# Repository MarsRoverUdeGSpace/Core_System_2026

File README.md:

# Core System 2026

Core electronics, embedded firmware, and ROS 2 integration workspace for the UdeG Space 2026 rover platform.

## Overview

This repository contains the validated `Kukulcan Rev A` controller hardware, the primary rover MCU firmware, and the ROS 2 workspace used to integrate the embedded system with the rest of the stack.

The current main firmware path, `kukulcan/firmware/upio-ros2/`, is a working ESP32-S3 implementation built on Arduino, FreeRTOS, and micro-ROS, with an AUTOSAR-inspired layered architecture deployed on real hardware.

This MCU sits at the intersection of the rover core system and the autonomous navigation stack for the Mars Rover UdeG Space Maya rover in URC 2026. It concentrates the odometry and control interfaces needed for vehicle state estimation and low-level motion integration, including wheel encoders, dual-IMU integration across the wider system, GNSS, altimeter data, communications with RoboClaw motor controllers, and communications with the main processing unit based on the NVIDIA Jetson Orin Nano.

The platform has already been validated on real hardware and is intended to continue system-level validation during field testing, including work planned for the Mars Desert Research Station.

## Current release state

This repository is past initial bring-up and already contains active work in four areas:

- `kukulcan/hardware/`: KiCad MCU design, 3D exports, fabrication outputs, and PCBA files for `MCU RevA`
- `kukulcan/firmware/upy/`: MicroPython-based sensor and UI bring-up
- `kukulcan/firmware/upio-ros2/`: ESP32-S3 PlatformIO firmware using Arduino, FreeRTOS, micro-ROS, and an AUTOSAR-inspired layered architecture
- `src/`: ROS 2 workspace with custom messages, a local `teleop_twistmux_node`, and vendored micro-ROS packages

As of June 2, 2026, this repository is the stable core-system release line for the rover MCU and ROS-facing embedded interface used by AutoNav.

Current status summary:

- hardware: validated RevA integration board with tracked manufacturing outputs
- firmware: stable release on real hardware with successful `pio run`
- localization interface: firmware-owned epoch-stamped `/odom`, direct BNO055 IMU, magnetometer, and GNSS streams validated on the Kukulcan PCB and consumed by the AutoNav stack
- ROS 2 workspace: active and buildable for the currently used packages
- control interface: `cmd_vel` response and motor timeout behavior corrected for the stable AutoNav integration path

Verified in this repository review:

- `colcon build --packages-select teleop_twistmux_node micro_ros_msgs drive_base_msgs`
- maintainer-provided successful `pio run` result for `upio-ros2`

## Stable release notes

This release promotes `feature/imu-mag-calibration` as the stable source line for `develop` and `main`.

Release highlights:

- integrated wheel odometry publication from RoboClaw encoder ticks
- added BNO055 magnetometer publishing for Jetson-side calibration and localization checks
- stabilized GNSS `NavSatFix`, IMU, magnetometer, and `/odom` timestamps in ROS epoch time
- made `/odom` reliable so full `nav_msgs/msg/Odometry` samples survive XRCE transport size limits
- bounded reliable publisher waits and scheduler catch-up behavior so delayed odometry acknowledgements do not starve IMU/GNSS publication
- calibrated odometry geometry and ticks-per-revolution values for the physical rover
- corrected `cmd_vel` response behavior and retained independent motor safety timeout handling

## Highlights

- `Kukulcan Rev A` is a 4-layer protected controller board built around an `ESP32-S3R8` with added `32 MB` flash
- the firmware architecture treats micro-ROS as the effective RTE boundary and FreeRTOS tasks as the application execution model
- the project has a reliable micro-ROS + FreeRTOS + Arduino implementation on the target MCU
- firmware `/odom` and direct IMU/GNSS topics now provide the validated inputs for Jetson-side EKF/global-localization testing
- the Jetson-side integration path is already designed into the hardware through the 40-pin expansion/control header

## Repository layout

| Path | Purpose |
| --- | --- |
| `kukulcan/hardware/` | MCU KiCad project, local libraries, manufacturing outputs |
| `kukulcan/firmware/` | Embedded firmware projects |
| `src/` | ROS 2 workspace packages and vendored dependencies |
| `docs/` | Datasheets, design notes, images, and release support material |
| `CONTRIBUTING.md` | Lightweight workflow and contribution rules |

## Primary subsystems

- Hardware: [kukulcan/hardware/README.md](kukulcan/hardware/README.md)
- Firmware: [kukulcan/firmware/README.md](kukulcan/firmware/README.md)
- Main firmware track: [kukulcan/firmware/upio-ros2/README.md](kukulcan/firmware/upio-ros2/README.md)

## Firmware architecture direction

The main embedded firmware track, `upio-ros2`, is not just an implementation of drivers and ROS transport. It is also the project's embedded software architecture reference:

- application logic is kept separate from hardware-facing details
- the runtime environment layer is effectively realized through the micro-ROS integration boundary
- hardware-dependent behavior is pushed into HAL-style modules and lower layers
- FreeRTOS tasking is used to preserve deterministic behavior across sensing, publishing, and actuation paths, effectively expressing the application layer execution model

That AUTOSAR-inspired separation is already a validated project strength and should be treated as part of the stable release narrative. The same applies to the reliable micro-ROS + FreeRTOS + Arduino implementation on the target MCU, which meaningfully reduces integration friction for the rover stack.

## Quick start

```bash
git clone git@github.com:MarsRoverUdeGSpace/Core_System_2026.git
cd Core_System_2026
git checkout main
```

ROS 2 packages can be listed with:

```bash
colcon list
```

The `upio-ros2` firmware lives in:

```bash
cd kukulcan/firmware/upio-ros2
pio run
```

The hardware project opens from:

```text
kukulcan/hardware/MCU/MCU.kicad_pro
```

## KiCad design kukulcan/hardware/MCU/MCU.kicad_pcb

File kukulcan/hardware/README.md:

# Kukulcan Hardware

This directory contains the MCU hardware design and tracked fabrication artifacts for the Kukulcan rover controller board.

Current documented board target: `Kukulcan Rev A`, described as validated RevA integration hardware.

## Contents

- `MCU/`: main KiCad project, board file, schematic, local outputs, and board exports
- `Libraries/`: shared symbols, footprints, and 3D models used by the design
- `mfr/`: tracked manufacturing outputs, Gerbers, drills, fab zip, BOM, and CPL

## Primary design files

- Project: `MCU/MCU.kicad_pro`
- Schematic: `MCU/MCU.kicad_sch`
- PCB: `MCU/MCU.kicad_pcb`
- Board solid: `MCU/MCU.stl`
- Exported board model: `MCU/outputs/MCU_board.step`
- Exported schematic PDF: `MCU/outputs/MCU_schematic.pdf`

## Board overview

Kukulcan Rev A is a 4-layer ESP32-based rover controller board intended to bridge embedded control, onboard sensing, and Jetson-side ROS integration.

Key design points:

- MCU: `ESP32-S3R8` with additional `32 MB` flash
- PCB size: `78 x 53 mm`
- PCB thickness: `1.6 mm`
- Copper weight: `1 oz`
- Surface finish: `HASL with lead`
- Mounting: `M3` mounting holes
- Debug/programming: USB JTAG support for programming and debugging

## Power architecture

The board uses a protected `5 V` input architecture with separate power intent for core electronics and auxiliary lighting.

- Allowed input: `5 V`
- Main power entry: two barrel-jack inputs
- Main regulated logic rail: `3.3 V` generated from `5 V` through a `TLV1117-33` LDO
- Auxiliary power rail: separate `5 V` rail for the LED strip
- Power implementation emphasis: three power planes across the 4-layer board

Documented protection features:

- fuse protection
- reverse-polarity protection
- ESD protection
- TVS protection

## Integrated and exposed interfaces

Integrated devices:

- GNSS: `u-blox NEO-M8N`, mounted directly on the PCB
- Barometer/environmental sensor: `BME280`
- IMU: `BNO055`

External connectivity:

- Jetson interface: `40-pin` header intended for ribbon-cable connection to the Jetson Orin Nano as a broader expansion/control interface
- Jetson link currently includes UART plus two GPIO lines connected to the ESP32
- Jetson-side dedicated I2C is reserved for the `BMI088` IMU
- RoboClaw communications: exposed UART
- Expansion bus: exposed I2C header for additional peripherals
- GNSS antenna: coaxial connector for an active GNSS antenna

Planned but not yet implemented:

- external `2.4"` diagnostics display on the exposed I2C bus

## Validation status

Kukulcan Rev A is validated RevA integration hardware.

Maintainer-reported validation status:

- stable embedded firmware can run on the board
- most hardware functions have been validated on real hardware
- GNSS validation is still pending
- diagnostics display support is still pending

## Manufacturing status

Tracked fabrication data already exists for `MCU RevA`:

- Gerbers and drills in `mfr/`
- Fabrication archive in `mfr/MCU_revA_fab.zip`
- Assembly files in `mfr/pcba/`

If the PCB changes, regenerate these outputs in the same commit or a clearly paired follow-up commit.

## Validation evidence

### PCB render

Current board render for Kukulcan Rev A.

### Real hardware

Assembled Kukulcan Rev A board photographed on real hardware.

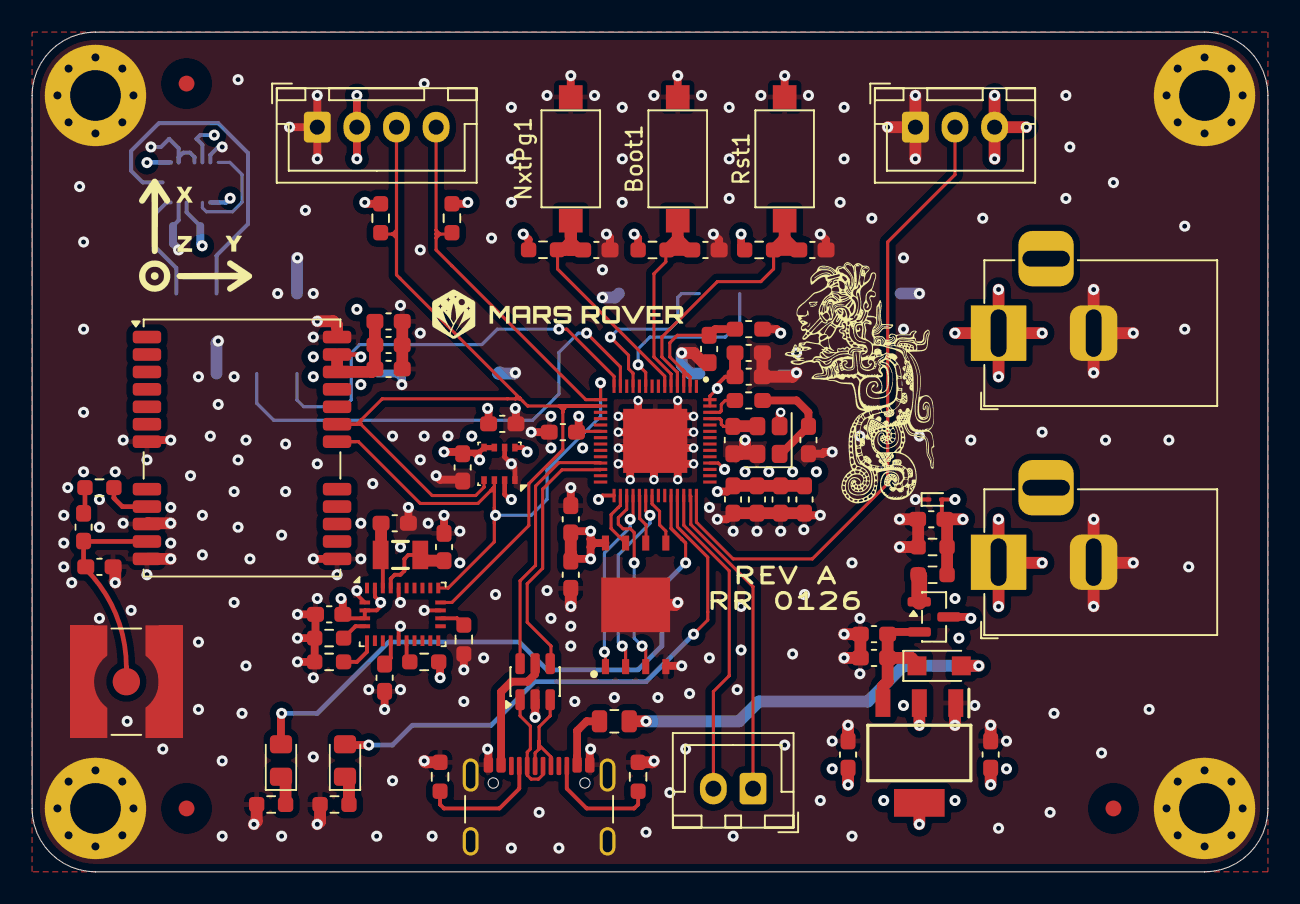
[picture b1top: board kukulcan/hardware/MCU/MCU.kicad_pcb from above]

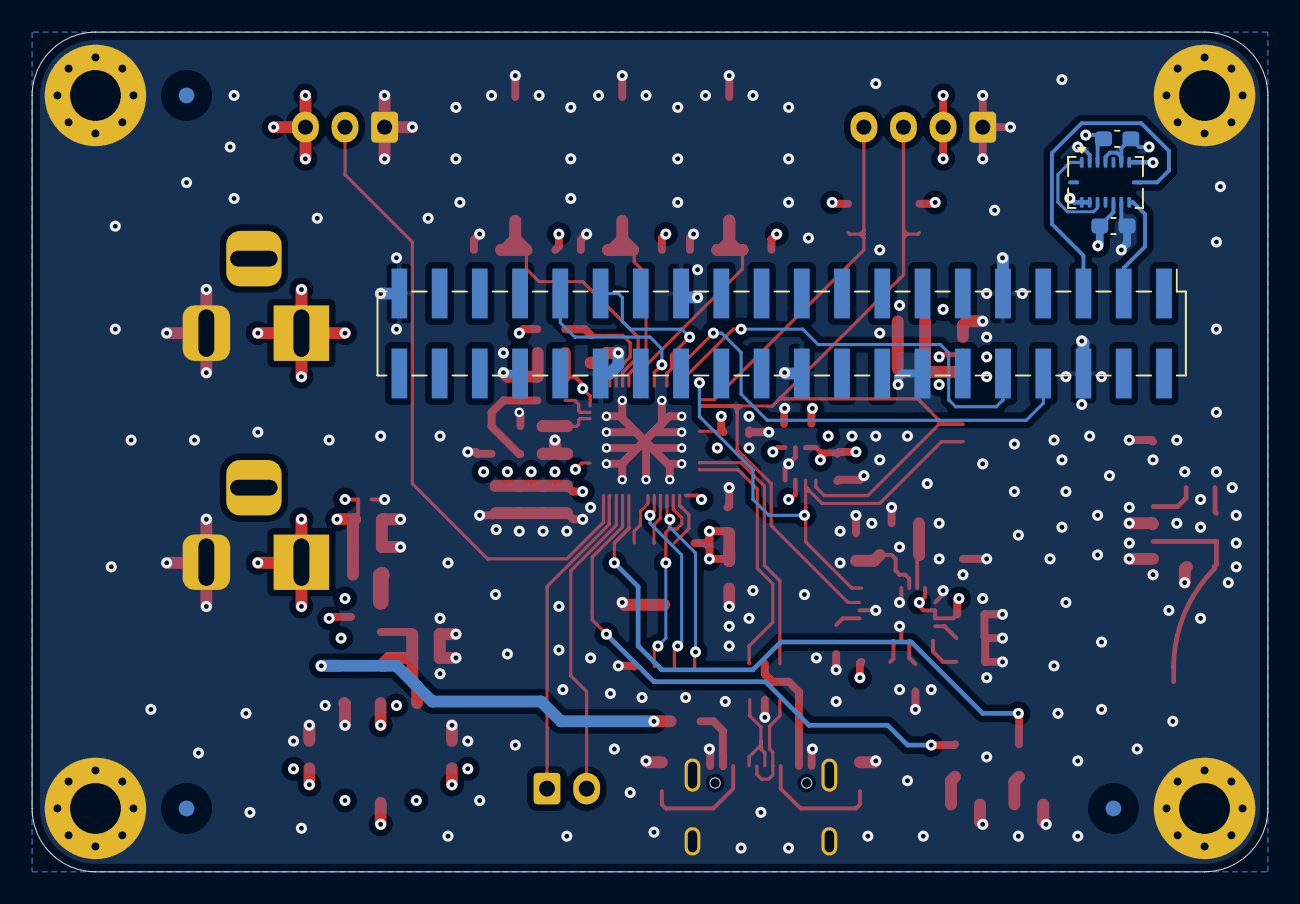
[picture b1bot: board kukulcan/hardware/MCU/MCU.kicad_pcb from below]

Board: 4 copper layers, 78.0 x 53.0 mm, 91 parts (7 on the bottom side), 50 nets.

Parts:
Boot1: SW_Push; SW_SPST_CK_RS282G05A3
C1, C2, C5, C9, C10, C13, C15, C21, C24, C25, C26, C27, C28, C29, C30, C31: 0.1uF; C_0603_1608Metric_Pad1.08x0.95mm_HandSolder
C3, C6: 1uF; C_0603_1608Metric_Pad1.08x0.95mm_HandSolder
C4, C11, C12, C14: 10uF; C_0603_1608Metric_Pad1.08x0.95mm_HandSolder
C7: 1uF/10V; C_0603_1608Metric_Pad1.08x0.95mm_HandSolder
C8: 10nF/10V; C_0603_1608Metric_Pad1.08x0.95mm_HandSolder
C16, C17: 22pF/10V; C_0603_1608Metric_Pad1.08x0.95mm_HandSolder
C18, C19, C20: 100nF; C_0603_1608Metric_Pad1.08x0.95mm_HandSolder
C22, C23: 22pF; C_0603_1608Metric_Pad1.08x0.95mm_HandSolder
C32: 10nF; C_0603_1608Metric_Pad1.08x0.95mm_HandSolder
D1: ESD9B5.0ST5G; D_SOD-923
D2: PMEG2010ER; Nexperia_CFP3_SOD-123W
D3: USBLC6-2SC6; SOT-23-6
F1: 6V/2A; Fuse_0805_2012Metric
FID1, FID2, FID3, FID4, FID5, FID6: Fiducial; Fiducial_1mm_Mask3mm
H1, H2, H3, H4: MountingHole_Pad; MountingHole_3.2mm_M3_Pad_Via
J1, J2: Barrel_Jack_5V_In; BarrelJack_Horizontal
J3: USB_C_Receptacle; USB_C_Receptacle_GCT_USB4105-xx-A_16P_TopMnt_Horizontal
J4: SMA_GNSS; SMA_Amphenol_132134-10_Vertical
Jetson1: Conn_02x20_Odd_Even; PinHeader_2x20_P2.54mm_Vertical_SMD
L1: 2nH; L_0603_1608Metric_Pad1.05x0.95mm_HandSolder
L2: 24nH; L_0603_1608Metric_Pad1.05x0.95mm_HandSolder
L3: 27nH; L_0603_1608Metric_Pad1.05x0.95mm_HandSolder
LED1: White; LED_0805_2012Metric_Pad1.15x1.40mm_HandSolder
LED2: Red; LED_0805_2012Metric_Pad1.15x1.40mm_HandSolder
LEDStrip1: JST XH 01x03; JST_XH_B3B-XH-A_1x03_P2.50mm_Vertical
NxtPg1: SW_Push; SW_SPST_CK_RS282G05A3
Oled1: JST XH 01x04; JST_XH_B4B-XH-A_1x04_P2.50mm_Vertical
Q1: AO3401A; SOT-23
R1, R10, R11, R12, R13, R15, R16: 10k/5%; R_0603_1608Metric_Pad0.98x0.95mm_HandSolder
R2, R3, R4: 1k/5%; R_0603_1608Metric_Pad0.98x0.95mm_HandSolder
R5, R6, R7, R8, R9: 5k1; R_0603_1608Metric_Pad0.98x0.95mm_HandSolder
R14: 10R/1%; R_0603_1608Metric_Pad0.98x0.95mm_HandSolder
RBCs1: JST XH 01x02 Ver; JST_XH_B2B-XH-A_1x02_P2.50mm_Vertical
Rst1: SW_Push; SW_SPST_CK_RS282G05A3
U1: TLV1117-33; SOT230P700X180-4N
U2: W25Q256JVEIQ
U3: ESP32-S3R8
U4: BNO055; LGA-28_5.2x3.8mm_P0.5mm
U5: NEO-M8N; ublox_NEO
U6: BMI088; Bosch_LGA-16_4.5x3mm_P0.5mm_LayoutBorder7x1y_ClockwisePinNu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
U7: BME280; Bosch_LGA-8_2.5x2.5mm_P0.65mm_ClockwisePinNumbering
X1: 40MHz; Crystal_SMD_2520-4Pin_2.5x2.0mm
Y1: 32.768kHz; Crystal_SMD_3.2x1.5mm
svg2mod: G***; kukulcan
svg2mod#2: G***; MarsRover
svg2mod#3: G***; IMU_Axes_XYZ

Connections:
+3V3: C2.1, C3.1, C4.1, C5.1, C6.1, C7.1, C8.1, C9.1, C10.1, C14.1, C15.1, C21.2, C24.1, C25.1, C26.1, C28.1, C29.1, C30.1, C31.1, L1.1, Oled1.2, R7.1, R8.1, R9.1, R10.1, R15.2, R16.2, U1.2 (VO), U1.4, U2.8 (VCC), U3.20 (VDD3P3_RTC), U3.29 (VDD_SPI), U3.46 (VDD3P3_CPU), U3.55 (VDDA), U3.56 (VDDA), U4.3 (VDD), U4.4 (~BOOT_LOAD_PIN), U4.28 (VDDIO), U5.22 (V_BCKP), U5.23 (VCC), U6.3 (VDD), U6.7 (PS), U6.11 (VDDIO), U6.14 (~CSB1), U6.15 (SDO1), U7.2 (CSB), U7.5 (SDO), U7.6 (VDDIO), U7.8 (VDD)
+RB_VDD_5V: J1.1, LEDStrip1.3
+VDD_5V: C11.1, D1.2 (A2), D2.2 (A), F1.2, J2.1, Q1.3 (D), R1.1, R2.1
+VUSB: D3.5 (VBUS), F1.1, J3.A4, J3.A9, J3.B4, J3.B9
/RF1: R14.1, U5.9 (VCC_RF)
/RF2: L3.1, R14.2
/RF_IN: C32.2, J4.1 (In), L3.2, U5.11 (RF_IN)
/USBCC1: J3.A5 (CC1), R6.1
/USBCC2: J3.B5 (CC2), R5.1
/USBCD+: D3.3 (I/O2), J3.A6 (D+), J3.B6 (D+)
/USBCD-: D3.1 (I/O1), J3.A7 (D-), J3.B7 (D-)
/USBD+: D3.4 (I/O2), U3.26 (GPIO20/USB_D+)
/USBD-: D3.6 (I/O1), U3.25 (GPIO19/USB_D-)
/XIN32: C23.2, U4.27 (XIN32), Y1.1
/XOUT32: C22.2, U4.26 (XOUT32), Y1.2
/XTAL_N: C17.1, U3.53 (XTAL_N), X1.3
/XTAL_P: L2.2, U3.54 (XTAL_P)
BOOT: Boot1.1, C18.1, R7.2, U3.5 (GPIO0)
GND: Boot1.2, C1.2, C2.2, C3.2, C4.2, C5.2, C6.2, C7.2, C8.2, C9.2, C10.2, C11.2, C12.2, C13.2, C14.2, C15.2, C16.1, C17.2, C18.2, C19.2, C20.2, C21.1, C22.1, C23.1, C24.2, C25.2, C26.2, C27.1, C28.2, C29.2, C30.2, C31.2, C32.1, D1.1 (A1), D3.2 (GND), H1.1, H2.1, H3.1, H4.1, J1.2, J2.2, J3.A1, J3.A12, J3.B1, J3.B12, J3.S1, J4.2 (Ext), Jetson1.6, Jetson1.9, Jetson1.14, Jetson1.20, Jetson1.25, Jetson1.30, Jetson1.34, Jetson1.39, LEDStrip1.1, NxtPg1.2, Oled1.1, R1.2, R3.1, R4.1, R5.2, R6.2, R11.1, R12.1, R13.1, Rst1.2, U1.1 (GND), U2.4 (GND), U2.9, U3.57 (GND), U4.2 (GND), U4.10 (BL_IND), U4.18 (COM2), U4.25 (GNDIO), U5.7 (VDD_USB), U5.10 (GND), U5.12 (GND), U5.13 (GND), U5.24 (GND), U6.2 (GNDA), U6.4 (GNDA), U6.6 (GNDIO), U6.10 (SDO2), U7.1 (GND), U7.7 (GND), X1.2, X1.4
JT_MCU1: Jetson1.29, U3.11 (GPIO6)
JT_MCU2: Jetson1.31, U3.9 (GPIO4)
JT_RX: Jetson1.10, U3.14 (GPIO9)
JT_TX: Jetson1.8, U3.13 (GPIO8)
LED_RED: LED2.2 (A), U3.39 (GPIO34)
LED_WHITE: LED1.2 (A), U3.38 (GPIO33)
LedStrip: LEDStrip1.2, U3.42 (GPIO37)
unnamed: C1.1, L1.2, U3.2 (VDD3P3), U3.3 (VDD3P3)
unnamed: C16.2, L2.1, X1.1
unnamed: C12.1, C13.1, D2.1 (K), Q1.2 (S), U1.3 (VI)
unnamed: LED1.1 (K), R3.2
unnamed: LED2.1 (K), R4.2
unnamed: Q1.1 (G), R2.2
unnamed: C27.2, U4.9 (CAP)
unnamed: R13.2, U4.17 (COM3)
unnamed: R11.2, U4.6 (PS0)
unnamed: R12.2, U4.5 (PS1)
unnamed: R10.2, U4.11 (~RESET)
unnamed: U6.1 (INT2), U6.13 (INT4)
NxtPg: C20.1, NxtPg1.1, R9.2, U3.6 (GPIO1)
RB_RX: RBCs1.1, U3.41 (GPIO36)
RB_TX: RBCs1.2, U3.40 (GPIO35)
RST: C19.1, R8.2, Rst1.1, U3.4 (CHIP_PU)
SCL: Jetson1.5, Oled1.3, R15.1, U3.16 (GPIO11), U4.19 (COM1), U5.19 (SCL/SPI_CLK), U6.8 (SCK/SCL), U7.4 (SCK)
SDA: Jetson1.3, Oled1.4, R16.1, U3.15 (GPIO10), U4.20 (COM0), U5.18 (SDA/~SPI_CS), U6.9 (SDI/SDA), U7.3 (SDI)
SPICLK: U2.6 (CLK), U3.33 (SPICLK)
SPICS0: U2.1 (~CS), U3.32 (SPICS0)
SPID: U2.5 (DI/IO_{0}), U3.35 (SPID)
SPIHD: U2.7 (~HOLD/~RESET/IO_{3}), U3.30 (SPIHD)
SPIQ: U2.2 (DO/IO_{1}), U3.34 (SPIQ)
SPIWP: U2.3 (~WP/IO_{2}), U3.31 (SPIWP)

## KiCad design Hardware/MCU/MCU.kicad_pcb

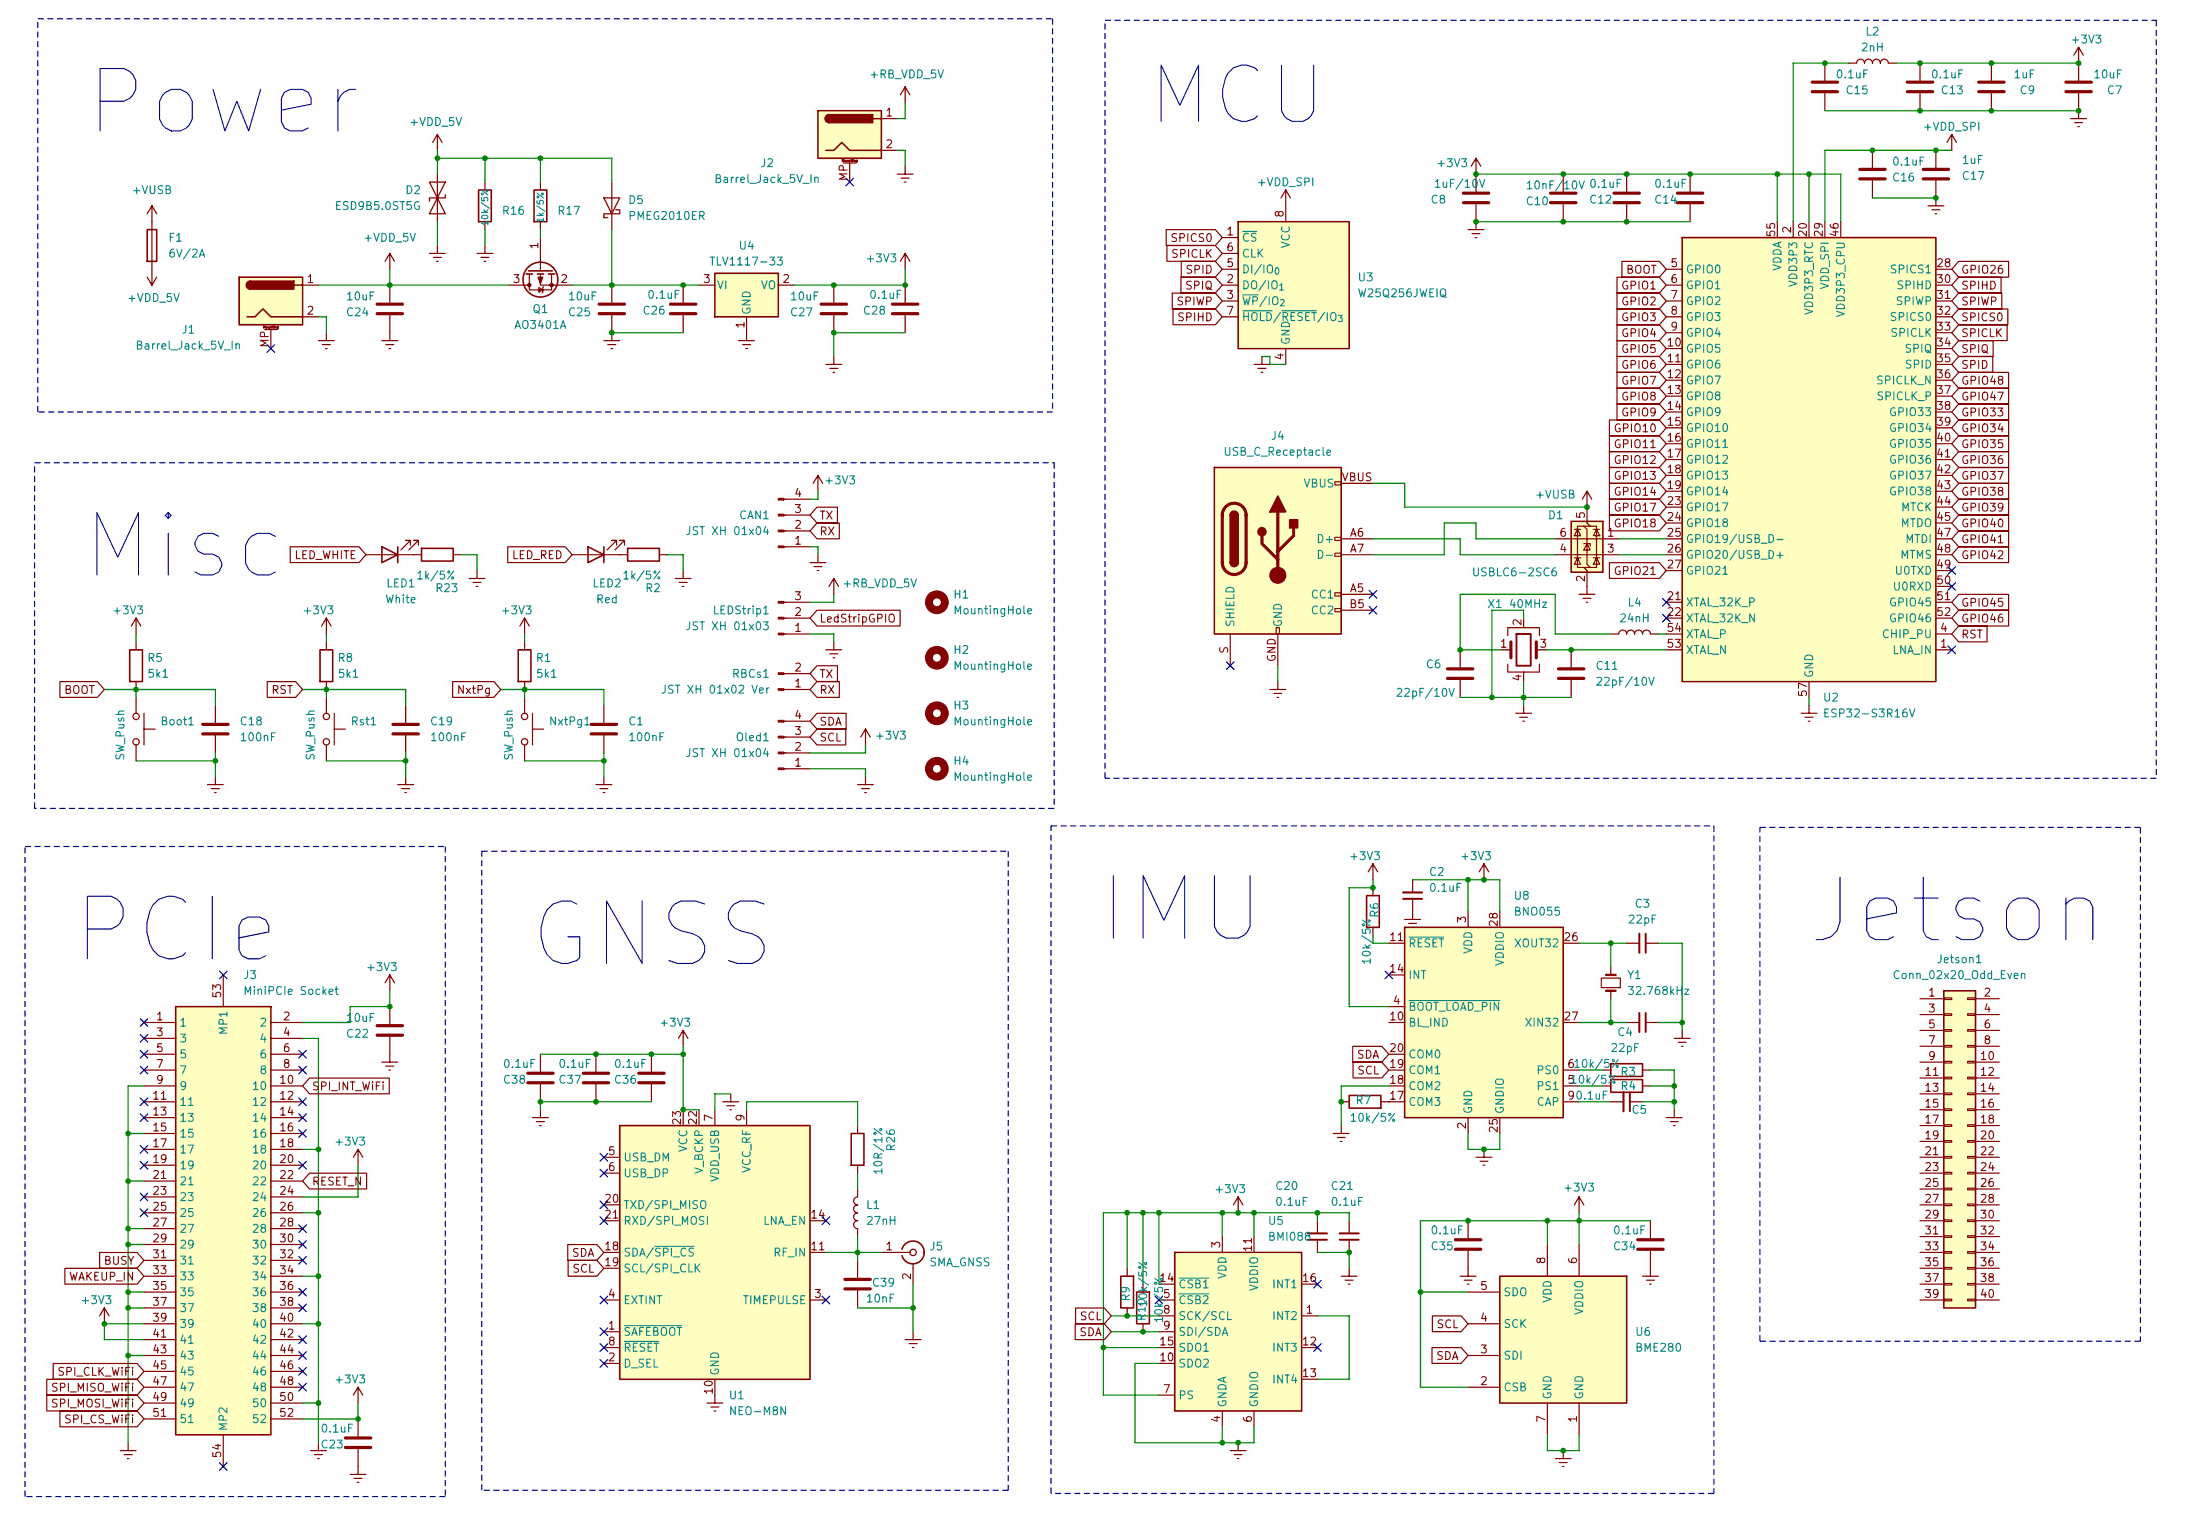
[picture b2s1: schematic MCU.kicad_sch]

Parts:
Boot1: SW_Push; SW_SPST_CK_RS282G05A3
C1, C18, C19: 100nF; C_0402_1005Metric_Pad0.74x0.62mm_HandSolder
C2, C5, C20, C21: 0.1uF; C_0402_1005Metric_Pad0.74x0.62mm_HandSolder; Voltage 1kV; Tolerance 100%
C3, C4: 22pF; C_0402_1005Metric_Pad0.74x0.62mm_HandSolder; Voltage 1kV; Tolerance 100%
C6, C11: 22pF/10V; C_0402_1005Metric_Pad0.74x0.62mm_HandSolder
C7, C22, C24, C25, C27: 10uF; C_0402_1005Metric_Pad0.74x0.62mm_HandSolder
C8: 1uF/10V; C_0402_1005Metric_Pad0.74x0.62mm_HandSolder
C9, C17: 1uF; C_0402_1005Metric_Pad0.74x0.62mm_HandSolder
C10: 10nF/10V; C_0402_1005Metric_Pad0.74x0.62mm_HandSolder
C12, C13, C14, C15, C16, C23, C26, C28, C34, C35, C36, C37, C38: 0.1uF; C_0402_1005Metric_Pad0.74x0.62mm_HandSolder
C39: 10nF; C_0402_1005Metric_Pad0.74x0.62mm_HandSolder
CAN1: JST XH 01x04; JST_XH_S4B-XH-SM4-TB_1x04-1MP_P2.50mm_Horizontal
D1: USBLC6-2SC6; SOT-23-6
D2: ESD9B5.0ST5G; D_SOD-923
D5: PMEG2010ER; Nexperia_CFP3_SOD-123W
F1: 6V/2A; Fuse_0402_1005Metric_Pad0.77x0.64mm_HandSolder
H1, H2, H3, H4: MountingHole; MountingHole_3.2mm_M3_Pad_Via
J1, J2: Barrel_Jack_5V_In; BarrelJack_Horizontal
J3: MiniPCIe Socket; MiniPCIeSocket; Mouser Part Number 571-2041119-1
J4: USB_C_Receptacle; USB-C_16
J5: SMA_GNSS; U.FL_Molex_MCRF_73412-0110_Vertical
Jetson1: Conn_02x20_Odd_Even; PinHeader_2x20_P2.54mm_Vertical_SMD
L1: 27nH; L_0402_1005Metric_Pad0.77x0.64mm_HandSolder
L2: 2nH; L_0402_1005Metric_Pad0.77x0.64mm_HandSolder
L4: 24nH; L_0402_1005Metric_Pad0.77x0.64mm_HandSolder
LED1: White; LED_1206_3216Metric_Pad1.42x1.75mm_HandSolder
LED2: Red; LED_1206_3216Metric_Pad1.42x1.75mm_HandSolder
LEDStrip1: JST XH 01x03; JST_XH_S3B-XH-SM4-TB_1x03-1MP_P2.50mm_Horizontal
NxtPg1: SW_Push; SW_SPST_CK_RS282G05A3
Oled1: JST XH 01x04; JST_XH_S4B-XH-SM4-TB_1x04-1MP_P2.50mm_Horizontal
Q1: AO3401A; SOT-23
R1, R5, R8: 5k1; R_0402_1005Metric_Pad0.72x0.64mm_HandSolder
R2, R17, R23: 1k/5%; R_0402_1005Metric_Pad0.72x0.64mm_HandSolder
R3, R4, R6, R7, R9, R10, R16: 10k/5%; R_0402_1005Metric_Pad0.72x0.64mm_HandSolder
R26: 10R/1%; R_0402_1005Metric_Pad0.72x0.64mm_HandSolder
RBCs1: JST XH 01x02 Ver; JST_XH_S2B-XH-A_1x02_P2.50mm_Horizontal
Rst1: SW_Push; SW_SPST_CK_RS282G05A3
U1: NEO-M8N; ublox_NEO
U2: ESP32-S3R16V
U3: W25Q256JWEIQ
U4: TLV1117-33; SOT230P700X180-4N
U5: BMI088; Bosch_LGA-16_4.5x3mm_P0.5mm_LayoutBorder7x1y_ClockwisePinNu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
U6: BME280; Bosch_LGA-8_2.5x2.5mm_P0.65mm_ClockwisePinNumbering
U8: BNO055; LGA-28_5.2x3.8mm_P0.5mm
X1: 40MHz; Crystal_SMD_2520-4Pin_2.5x2.0mm
Y1: 32.768kHz; Crystal_SMD_3.2x1.5mm

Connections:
+3V3: C2.2, C7.1, C8.1, C9.1, C10.1, C12.1, C13.1, C14.1, C20.2, C21.2, C22.1, C23.1, C27.1, C28.1, C34.1, C35.1, C36.1, C37.1, C38.1, CAN1.4, J3.2, J3.24, J3.39, J3.41, J3.52, L2.1, Oled1.2, R1.1, R5.1, R6.1, R8.1, R9.2, R10.2, U1.22 (V_BCKP), U1.23 (VCC), U2.20 (VDD3P3_RTC), U2.46 (VDD3P3_CPU), U2.55 (VDDA), U2.56 (VDDA), U4.2 (VO), U5.3 (VDD), U5.7 (PS), U5.11 (VDDIO), U5.14 (~CSB1), U5.15 (SDO1), U6.2 (CSB), U6.5 (SDO), U6.6 (VDDIO), U6.8 (VDD), U8.3 (VDD), U8.4 (~BOOT_LOAD_PIN), U8.28 (VDDIO)
+RB_VDD_5V: J2.1, LEDStrip1.3
+VDD_5V: C24.1, D2.2 (A2), D5.2 (A), F1.2, J1.1, Q1.3 (D), R16.1, R17.1
+VDD_SPI: C16.1, C17.1, U2.29 (VDD_SPI), U3.8 (VCC)
+VUSB: D1.5 (VBUS), F1.1, J4.VBUS
BOOT: Boot1.1, C18.1, R5.2, U2.5 (GPIO0)
BUSY: J3.31
GND: Boot1.2, C1.2, C2.1, C3.1, C4.1, C5.1, C6.1, C7.2, C8.2, C9.2, C10.2, C11.2, C12.2, C13.2, C14.2, C15.2, C16.2, C17.2, C18.2, C19.2, C20.1, C21.1, C22.2, C23.2, C24.2, C25.2, C26.2, C27.2, C28.2, C34.2, C35.2, C36.2, C37.2, C38.2, C39.1, CAN1.1, D1.2 (GND), D2.1 (A1), J1.2, J2.2, J3.4, J3.9, J3.15, J3.18, J3.21, J3.26, J3.27, J3.29, J3.34, J3.35, J3.37, J3.40, J3.43, J3.50, J4.GND, J5.2 (Ext), LEDStrip1.1, NxtPg1.2, Oled1.1, R2.1, R3.1, R4.1, R7.1, R16.2, R23.1, Rst1.2, U1.7 (VDD_USB), U1.10 (GND), U1.12 (GND), U1.13 (GND), U1.24 (GND), U2.57 (GND), U3.4 (GND), U4.1 (GND), U5.2 (GNDA), U5.4 (GNDA), U5.6 (GNDIO), U5.10 (SDO2), U6.1 (GND), U6.7 (GND), U8.2 (GND), U8.18 (COM2), U8.25 (GNDIO), X1.2, X1.4
GPIO1: U2.6 (GPIO1)
GPIO2: U2.7 (GPIO2)
GPIO3: U2.8 (GPIO3)
GPIO4: U2.9 (GPIO4)
GPIO5: U2.10 (GPIO5)
GPIO6: U2.11 (GPIO6)
GPIO7: U2.12 (GPIO7)
GPIO8: U2.13 (GPIO8)
GPIO9: U2.14 (GPIO9)
GPIO10: U2.15 (GPIO10)
GPIO11: U2.16 (GPIO11)
GPIO12: U2.17 (GPIO12)
GPIO13: U2.18 (GPIO13)
GPIO14: U2.19 (GPIO14)
GPIO17: U2.23 (GPIO17)
GPIO18: U2.24 (GPIO18)
GPIO21: U2.27 (GPIO21)
GPIO26: U2.28 (SPICS1)
GPIO33: U2.38 (GPIO33)
GPIO34: U2.39 (GPIO34)
GPIO35: U2.40 (GPIO35)
GPIO36: U2.41 (GPIO36)
GPIO37: U2.42 (GPIO37)
GPIO38: U2.43 (GPIO38)
GPIO39: U2.44 (MTCK)
GPIO40: U2.45 (MTDO)
GPIO41: U2.47 (MTDI)
GPIO42: U2.48 (MTMS)
GPIO45: U2.51 (GPIO45)
GPIO46: U2.52 (GPIO46)
GPIO47: U2.37 (SPICLK_P)
GPIO48: U2.36 (SPICLK_N)
LED_RED: LED2.2 (A)
LED_WHITE: LED1.2 (A)
LedStripGPIO: LEDStrip1.2
unnamed: C6.2, L4.1, X1.1
unnamed: C15.1, L2.2, U2.2 (VDD3P3), U2.3 (VDD3P3)
unnamed: D1.6 (I/O1), J4.A7 (D-), J4.B7 (D-)
unnamed: D1.4 (I/O2), J4.A6 (D+), J4.B6 (D+)
unnamed: C25.1, C26.1, D5.1 (K), Q1.2 (S), U4.3 (VI)
unnamed: C39.2, J5.1 (In), L1.2, U1.11 (RF_IN)
unnamed: L1.1, R26.2
unnamed: LED1.1 (K), R23.2
unnamed: LED2.1 (K), R2.2
unnamed: Q1.1 (G), R17.2
unnamed: R26.1, U1.9 (VCC_RF)
unnamed: D1.1 (I/O1), U2.25 (GPIO19/USB_D-)
unnamed: D1.3 (I/O2), U2.26 (GPIO20/USB_D+)
unnamed: C11.1, U2.53 (XTAL_N), X1.3
unnamed: L4.2, U2.54 (XTAL_P)
unnamed: U5.1 (INT2), U5.13 (INT4)
unnamed: C5.2, U8.9 (CAP)
unnamed: R7.2, U8.17 (COM3)
unnamed: R3.2, U8.6 (PS0)
unnamed: R4.2, U8.5 (PS1)
unnamed: C4.2, U8.27 (XIN32), Y1.1
unnamed: C3.2, U8.26 (XOUT32), Y1.2
unnamed: R6.2, U8.11 (~RESET)
NxtPg: C1.1, NxtPg1.1, R1.2
RESET_N: J3.22
RST: C19.1, R8.2, Rst1.1, U2.4 (CHIP_PU)
RX: CAN1.2, RBCs1.1
SCL: Oled1.3, R9.1, U1.19 (SCL/SPI_CLK), U5.8 (SCK/SCL), U6.4 (SCK), U8.19 (COM1)
SDA: Oled1.4, R10.1, U1.18 (SDA/~SPI_CS), U5.9 (SDI/SDA), U6.3 (SDI), U8.20 (COM0)
SPICLK: U2.33 (SPICLK), U3.6 (CLK)
SPICS0: U2.32 (SPICS0), U3.1 (~CS)
SPID: U2.35 (SPID), U3.5 (DI/IO_{0})
SPIHD: U2.30 (SPIHD), U3.7 (~HOLD/~RESET/IO_{3})
SPIQ: U2.34 (SPIQ), U3.2 (DO/IO_{1})
SPIWP: U2.31 (SPIWP), U3.3 (~WP/IO_{2})
SPI_CLK_WiFi: J3.45
SPI_CS_WiFi: J3.51
SPI_INT_WiFi: J3.10
SPI_MISO_WiFi: J3.47
SPI_MOSI_WiFi: J3.49
TX: CAN1.3, RBCs1.2
WAKEUP_IN: J3.33

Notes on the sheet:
Power
MCU
Jetson
GNSS
IMU
PCIe
Misc

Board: 4 copper layers, 84 parts (6 on the bottom side), 42 nets, no tracks yet.

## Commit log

2025-08-03 misc: add CODEOWNERS (self-reviewer)
2025-08-04 docs: add README overhaul + brief CONTRIBUTING guide
2025-08-04 chore: extend .gitignore for PlatformIO/Arduino build output
2025-08-04 chore: extend .gitignore for PlatformIO/Arduino build output (#2)
2025-08-04 docs: expand CONTRIBUTING with workflow update
2025-08-04 docs: expand CONTRIBUTING with workflow update (#3)
2025-08-11 feat(sw-coreio): seed PlatformIO projects and HAL stubs
2025-09-19 feat(sw-diagnostic-ui):improvements in diagnostic interface
2025-09-19 feat(sw-diagnostic-ui): add readme
2025-12-07 feat(hw-kukulcan): integrate current MCU board version
2025-12-07 chore(repo): normalize layout to kukulcan/{hardware,firmware} and docs/
2025-12-07 chore(repo): reset .gitignore for KiCad, firmware, Python, and ROS 2 workspace
2025-12-07 chore(repo): upy firmware reorganize
2025-12-07 docs(readme): document new layout and branch workflow
2025-12-07 chore(gitignore): ignore upstream micro-ROS dependencies in src/
2025-12-07 feat(kukulcan-fw): add upio_ros2 firmware skeleton
2025-12-08 feat(kukulcan-fw): add upio_ros2 firmware minimal RTE
2025-12-08 feat(kukulcan-fw): add upio_ros2 firmware minimal app
2025-12-08 feat(kukulcan-fw): add upio_ros2 firmware minimal app with FreeRTOS
2025-12-09 feat(kukulcan-fw): add upio_ros2 firmware config layer, uart pin config, and tested in target Jetsono Orin Nano
2025-12-09 docs(datasheets): esp32-s3 datasheet and user manual
2025-12-15 feat(kukulcan-hw): 3D models lfs pointer fix
2025-12-17 feat(kukulcan): several layout and schematic improvements, tasks pending. PCIe connector out.
2025-12-21 feat(kukulcan): current beta
2025-12-31 feat(kukulcan): final schematic draft
2026-01-09 feat(kukulcan): partial final PCB draft, GNSS pending
2026-01-16 docs(repo): add repository guidelines
2026-01-16 hw(libs): update footprints and 3d models
2026-01-16 hw(mcu): update schematic and pcb
2026-01-16 hw(mfr): add MCU RevA manufacturing outputs
2026-01-16 chore(lfs): track stl exports
2026-01-16 chore(lfs): store mcu stl in lfs
2026-01-16 docs(repo): clarify hardware exports and lfs
2026-01-18 fix(kukulcan): I2C impedance change design error fix
2026-01-18 feat(fw): sync firmware beta from feature/firmware
2026-01-28 fix(kukulcan): led resistors fix
2026-02-02 feat(kukulcan): roboclaw functionality validation
2026-02-04 feat(kukulcan-fw): add Kukulcan PCB bringup + open-loop cmd_vel
2026-02-04 fix(kukulcan): led resistors fix2
2026-02-04 feat(kukulcan): I2C bus and BME280 bring up
2026-02-04 fix(kukulcan): micro-ros RCSOFTCHECK bringup and leds diagnosis
2026-02-05 feat(kukulcan): IMU bringup, 50Hz rate, micro-ros real-time feat
2026-02-05 misc: code clean up
2026-02-09 feat(kukulcan): rte soft reinit on disconnect
2026-02-13 fix(kukulcan): i2c pull-up
2026-02-14 feat(core) teleop_mux joy node
2026-02-18 feat(core) hal led status driver
2026-03-07 fix diff turn
2026-03-09 feat(kukulcan-fw): add RoboClaw M1 encoder HAL and raw publishers
2026-03-09 chore(release): prepare v2.0.0-beta.2
2026-05-04 Typos fix
2026-05-07 feat(fw): add GNSS NavSatFix publisher
2026-06-03 release: promote stable core system
